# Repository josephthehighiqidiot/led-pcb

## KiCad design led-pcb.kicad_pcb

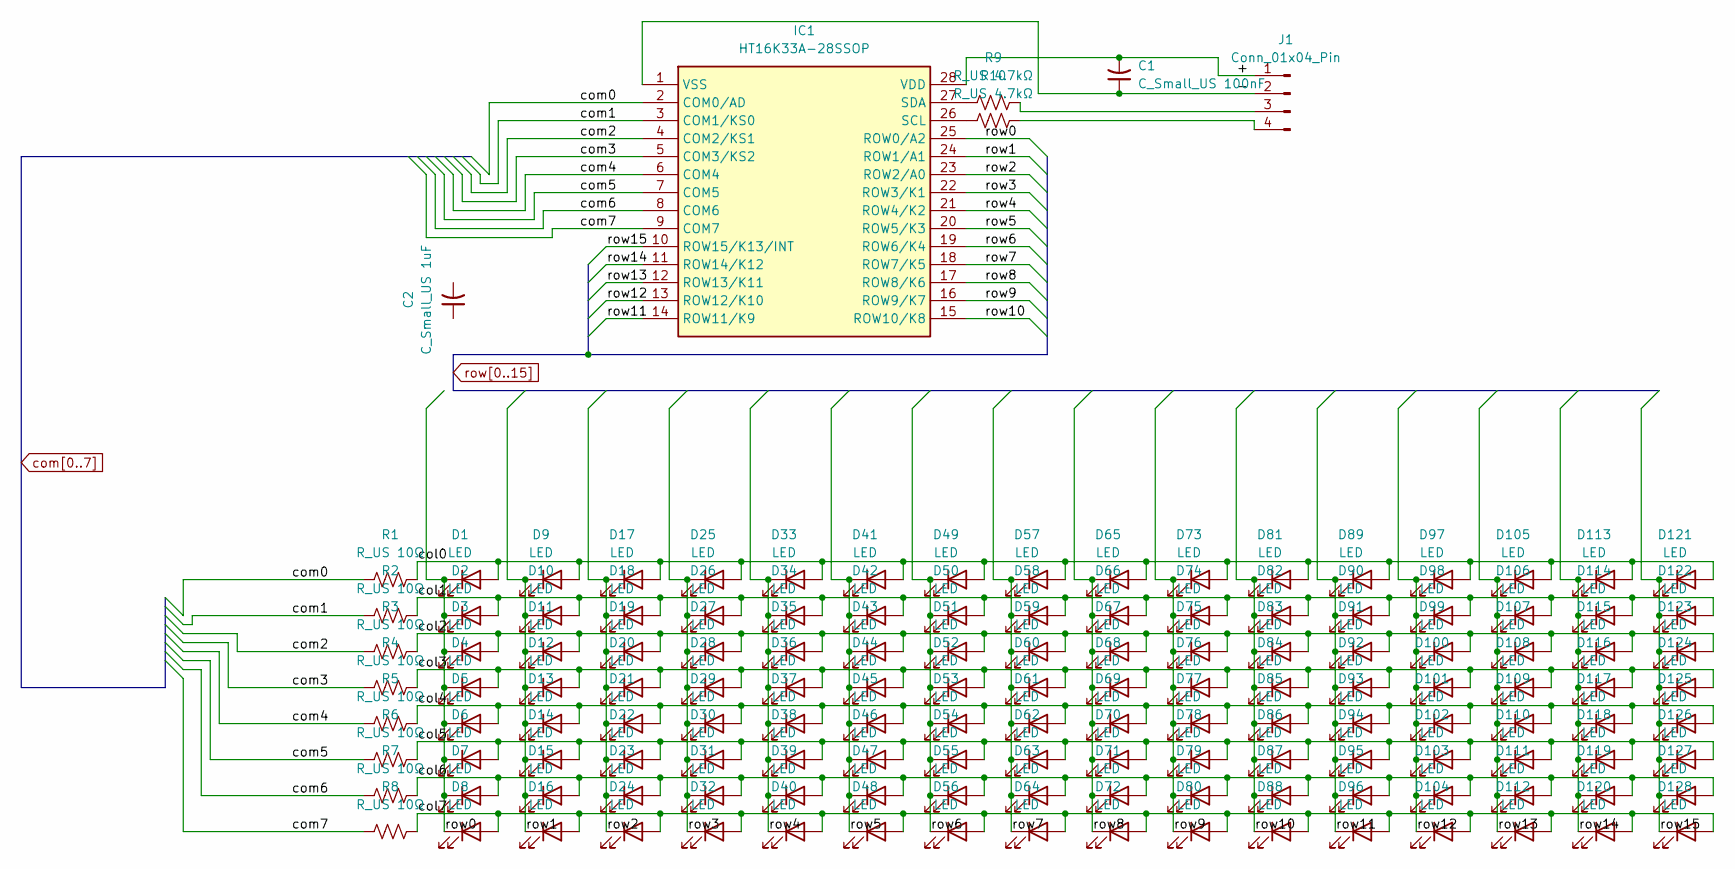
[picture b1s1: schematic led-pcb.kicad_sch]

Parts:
C1: C_Small_US 100nF; C_0805_2012Metric_Pad1.18x1.45mm_HandSolder
C2: C_Small_US 1uF; C_0805_2012Metric_Pad1.18x1.45mm_HandSolder
D1, D2, D3, D4, D5, D6, D7, D8, D9, D10, D11, D12, D13, D14, D15, D16, D17, D18, D19, D20, D21, D22, D23, D24, D25, D26, D27, D28, D29, D30, D31, D32, D33, D34, D35, D36, D37, D38, D39, D40, D41, D42, D43, D44, D45, D46, D47, D48, D49, D50, D51, D52, D53, D54, D55, D56, D57, D58, D59, D60, D61, D62, D63, D64, D65, D66, D67, D68, D69, D70, D71, D72, D73, D74, D75, D76, D77, D78, D79, D80, D81, D82, D83, D84, D85, D86, D87, D88, D89, D90, D91, D92, D93, D94, D95, D96, D97, D98, D99, D100, D101, D102, D103, D104, D105, D106, D107, D108, D109, D110, D111, D112, D113, D114, D115, D116, D117, D118, D119, D120, D121, D122, D123, D124, D125, D126, D127, D128: LED; LED_0805_2012Metric_Pad1.15x1.40mm_HandSolder
IC1: HT16K33A-28SSOP; SOP64P600X175-28N; Manufacturer_Part_Number HT16K33A-28SSOP
J1: Conn_01x04_Pin; PinSocket_1x04_P2.54mm_Vertical
R1, R2, R3, R4, R5, R6, R7, R8: R_US 10Ω; R_0805_2012Metric_Pad1.20x1.40mm_HandSolder
R9, R10: R_US 4.7kΩ; R_0805_2012Metric_Pad1.20x1.40mm_HandSolder

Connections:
/+: C1.2, IC1.28 (VDD), J1.1
/-: C1.1, IC1.1 (VSS), J1.2
/col0: D1.2 (A), D9.2 (A), D17.2 (A), D25.2 (A), D33.2 (A), D41.2 (A), D49.2 (A), D57.2 (A), D65.2 (A), D73.2 (A), D81.2 (A), D89.2 (A), D97.2 (A), D105.2 (A), D113.2 (A), D121.2 (A), R1.2
/col1: D2.2 (A), D10.2 (A), D18.2 (A), D26.2 (A), D34.2 (A), D42.2 (A), D50.2 (A), D58.2 (A), D66.2 (A), D74.2 (A), D82.2 (A), D90.2 (A), D98.2 (A), D106.2 (A), D114.2 (A), D122.2 (A), R2.2
/col2: D3.2 (A), D11.2 (A), D19.2 (A), D27.2 (A), D35.2 (A), D43.2 (A), D51.2 (A), D59.2 (A), D67.2 (A), D75.2 (A), D83.2 (A), D91.2 (A), D99.2 (A), D107.2 (A), D115.2 (A), D123.2 (A), R3.2
/col3: D4.2 (A), D12.2 (A), D20.2 (A), D28.2 (A), D36.2 (A), D44.2 (A), D52.2 (A), D60.2 (A), D68.2 (A), D76.2 (A), D84.2 (A), D92.2 (A), D100.2 (A), D108.2 (A), D116.2 (A), D124.2 (A), R4.2
/col4: D5.2 (A), D13.2 (A), D21.2 (A), D29.2 (A), D37.2 (A), D45.2 (A), D53.2 (A), D61.2 (A), D69.2 (A), D77.2 (A), D85.2 (A), D93.2 (A), D101.2 (A), D109.2 (A), D117.2 (A), D125.2 (A), R5.2
/col5: D6.2 (A), D14.2 (A), D22.2 (A), D30.2 (A), D38.2 (A), D46.2 (A), D54.2 (A), D62.2 (A), D70.2 (A), D78.2 (A), D86.2 (A), D94.2 (A), D102.2 (A), D110.2 (A), D118.2 (A), D126.2 (A), R6.2
/col6: D7.2 (A), D15.2 (A), D23.2 (A), D31.2 (A), D39.2 (A), D47.2 (A), D55.2 (A), D63.2 (A), D71.2 (A), D79.2 (A), D87.2 (A), D95.2 (A), D103.2 (A), D111.2 (A), D119.2 (A), D127.2 (A), R7.2
/col7: D8.2 (A), D16.2 (A), D24.2 (A), D32.2 (A), D40.2 (A), D48.2 (A), D56.2 (A), D64.2 (A), D72.2 (A), D80.2 (A), D88.2 (A), D96.2 (A), D104.2 (A), D112.2 (A), D120.2 (A), D128.2 (A), R8.2
unnamed: IC1.26 (SCL), R10.1
unnamed: IC1.27 (SDA), R9.1
unnamed: J1.3, R9.2
unnamed: J1.4, R10.2
com0: IC1.2 (COM0/AD), R1.1
com1: IC1.3 (COM1/KS0), R2.1
com2: IC1.4 (COM2/KS1), R3.1
com3: IC1.5 (COM3/KS2), R4.1
com4: IC1.6 (COM4), R5.1
com5: IC1.7 (COM5), R6.1
com6: IC1.8 (COM6), R7.1
com7: IC1.9 (COM7), R8.1
row0: D1.1 (K), D2.1 (K), D3.1 (K), D4.1 (K), D5.1 (K), D6.1 (K), D7.1 (K), D8.1 (K), IC1.25 (ROW0/A2)
row1: D9.1 (K), D10.1 (K), D11.1 (K), D12.1 (K), D13.1 (K), D14.1 (K), D15.1 (K), D16.1 (K), IC1.24 (ROW1/A1)
row2: D17.1 (K), D18.1 (K), D19.1 (K), D20.1 (K), D21.1 (K), D22.1 (K), D23.1 (K), D24.1 (K), IC1.23 (ROW2/A0)
row3: D25.1 (K), D26.1 (K), D27.1 (K), D28.1 (K), D29.1 (K), D30.1 (K), D31.1 (K), D32.1 (K), IC1.22 (ROW3/K1)
row4: D33.1 (K), D34.1 (K), D35.1 (K), D36.1 (K), D37.1 (K), D38.1 (K), D39.1 (K), D40.1 (K), IC1.21 (ROW4/K2)
row5: D41.1 (K), D42.1 (K), D43.1 (K), D44.1 (K), D45.1 (K), D46.1 (K), D47.1 (K), D48.1 (K), IC1.20 (ROW5/K3)
row6: D49.1 (K), D50.1 (K), D51.1 (K), D52.1 (K), D53.1 (K), D54.1 (K), D55.1 (K), D56.1 (K), IC1.19 (ROW6/K4)
row7: D57.1 (K), D58.1 (K), D59.1 (K), D60.1 (K), D61.1 (K), D62.1 (K), D63.1 (K), D64.1 (K), IC1.18 (ROW7/K5)
row8: D65.1 (K), D66.1 (K), D67.1 (K), D68.1 (K), D69.1 (K), D70.1 (K), D71.1 (K), D72.1 (K), IC1.17 (ROW8/K6)
row9: D73.1 (K), D74.1 (K), D75.1 (K), D76.1 (K), D77.1 (K), D78.1 (K), D79.1 (K), D80.1 (K), IC1.16 (ROW9/K7)
row10: D81.1 (K), D82.1 (K), D83.1 (K), D84.1 (K), D85.1 (K), D86.1 (K), D87.1 (K), D88.1 (K), IC1.15 (ROW10/K8)
row11: D89.1 (K), D90.1 (K), D91.1 (K), D92.1 (K), D93.1 (K), D94.1 (K), D95.1 (K), D96.1 (K), IC1.14 (ROW11/K9)
row12: D97.1 (K), D98.1 (K), D99.1 (K), D100.1 (K), D101.1 (K), D102.1 (K), D103.1 (K), D104.1 (K), IC1.13 (ROW12/K10)
row13: D105.1 (K), D106.1 (K), D107.1 (K), D108.1 (K), D109.1 (K), D110.1 (K), D111.1 (K), D112.1 (K), IC1.12 (ROW13/K11)
row14: D113.1 (K), D114.1 (K), D115.1 (K), D116.1 (K), D117.1 (K), D118.1 (K), D119.1 (K), D120.1 (K), IC1.11 (ROW14/K12)
row15: D121.1 (K), D122.1 (K), D123.1 (K), D124.1 (K), D125.1 (K), D126.1 (K), D127.1 (K), D128.1 (K), IC1.10 (ROW15/K13/INT)

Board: 2 copper layers, 142 parts (0 on the bottom side), 38 nets, no tracks yet.

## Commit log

2025-12-10 Fix corrupted content in README.md
    Remove corrupted lines from README.md
